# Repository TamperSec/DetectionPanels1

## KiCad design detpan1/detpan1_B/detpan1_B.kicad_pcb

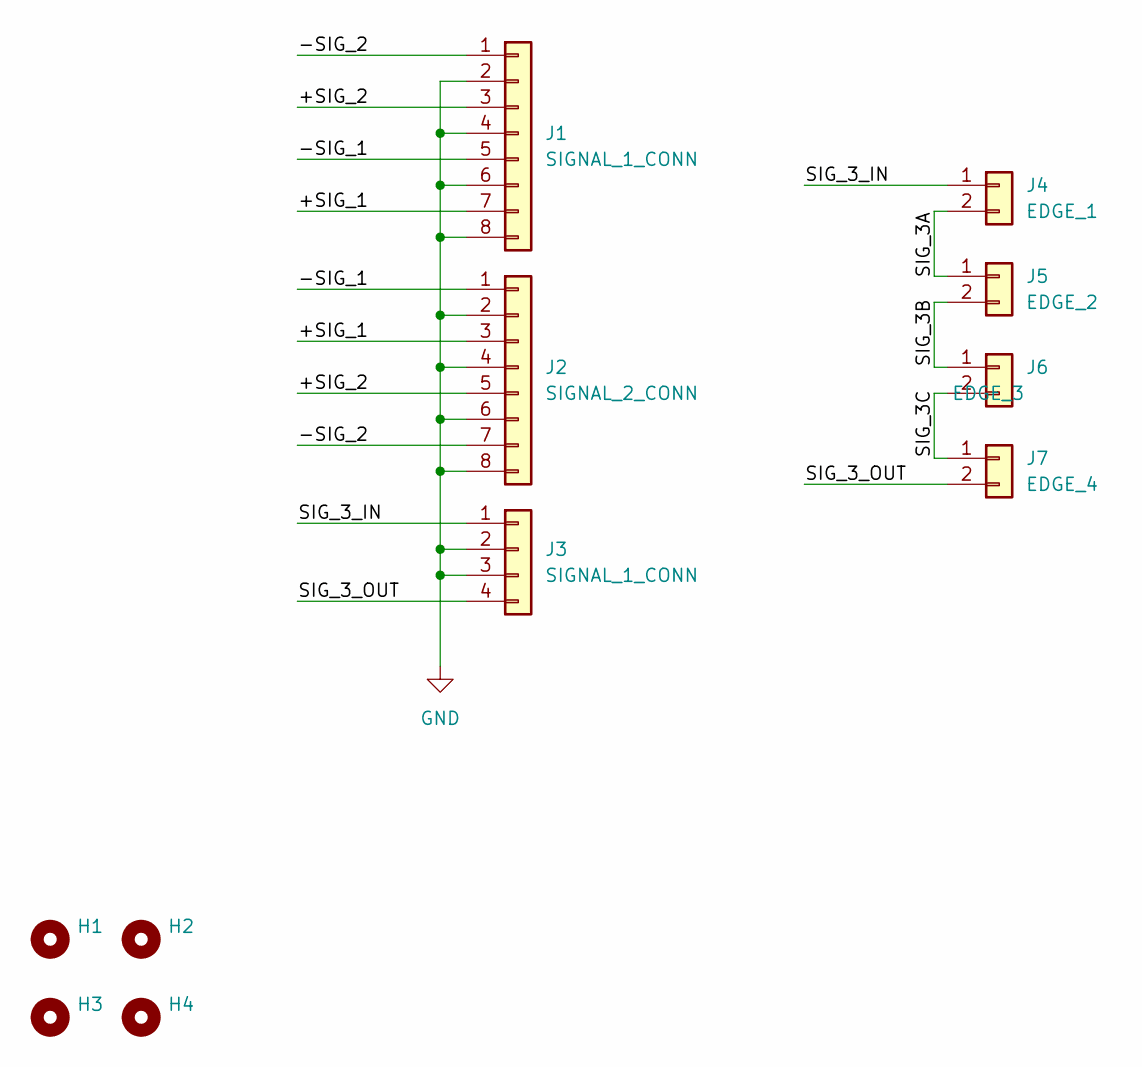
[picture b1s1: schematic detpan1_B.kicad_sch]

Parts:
H1, H2, H3, H4: MountingHole_3.2mm_M3
J1: SIGNAL_1_CONN; JST_GH_BM08B-GHS-TBT_1x08-1MP_P1.25mm_Vertical
J2: SIGNAL_2_CONN; JST_GH_BM08B-GHS-TBT_1x08-1MP_P1.25mm_Vertical
J3: SIGNAL_1_CONN; JST_GH_BM04B-GHS-TBT_1x04-1MP_P1.25mm_Vertical; JLCPCB Part # C225120
J4: EDGE_1; EDGE_CONN_IO
J5: EDGE_2; EDGE_CONN_IO
J6: EDGE_3; EDGE_CONN_IO
J7: EDGE_4; EDGE_CONN_IO

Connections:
/+SIG_1: J1.7, J2.3
/+SIG_2: J1.3, J2.5
/-SIG_1: J1.5, J2.1
/-SIG_2: J1.1, J2.7
/SIG_3A: J4.2, J5.1
/SIG_3B: J5.2, J6.1
/SIG_3C: J6.2, J7.1
/SIG_3_IN: J3.1, J4.1
/SIG_3_OUT: J3.4, J7.2
GND: J1.2, J1.4, J1.6, J1.8, J2.2, J2.4, J2.6, J2.8, J3.2, J3.3

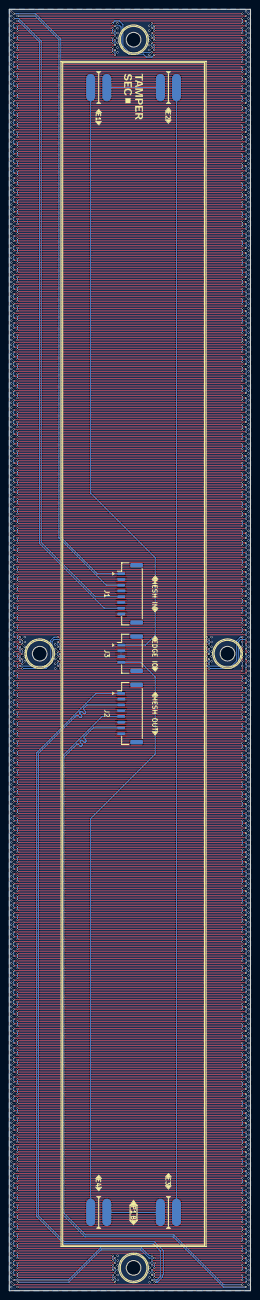
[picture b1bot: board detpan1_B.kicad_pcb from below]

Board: 4 copper layers, 52.4 x 278.4 mm, 11 parts (7 on the bottom side), 10 nets.

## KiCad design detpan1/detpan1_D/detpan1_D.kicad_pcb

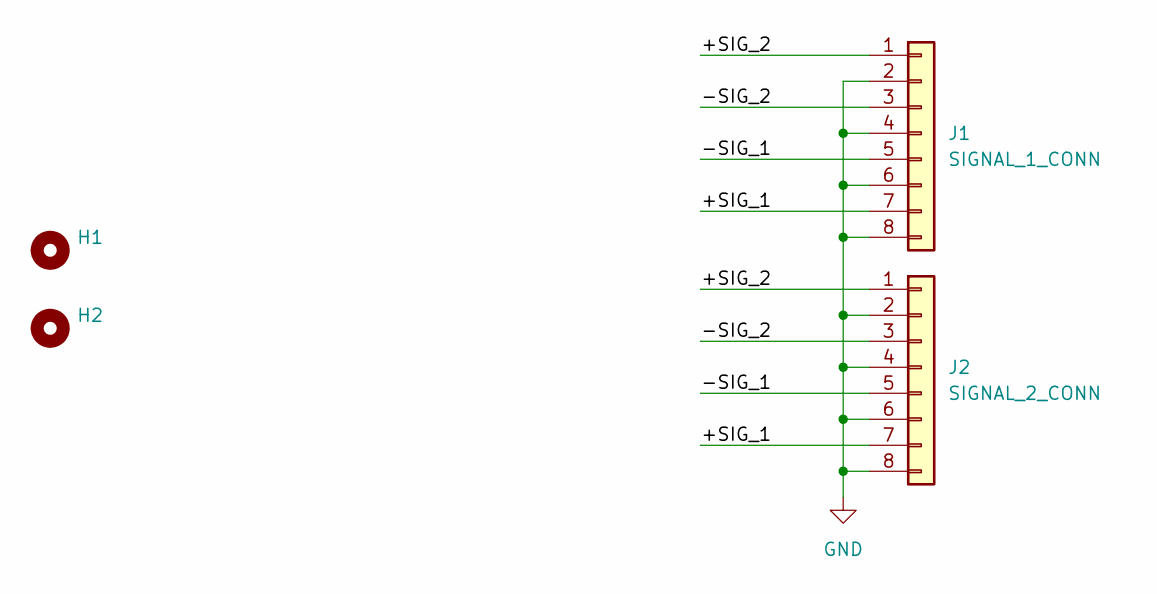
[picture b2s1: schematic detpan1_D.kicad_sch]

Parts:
H1, H2: MountingHole_3.2mm_M3
J1: SIGNAL_1_CONN; JST_GH_BM08B-GHS-TBT_1x08-1MP_P1.25mm_Vertical
J2: SIGNAL_2_CONN; JST_GH_BM08B-GHS-TBT_1x08-1MP_P1.25mm_Vertical

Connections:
/+SIG_1: J1.7, J2.7
/+SIG_2: J1.1, J2.1
/-SIG_1: J1.5, J2.5
/-SIG_2: J1.3, J2.3
GND: J1.2, J1.4, J1.6, J1.8, J2.2, J2.4, J2.6, J2.8

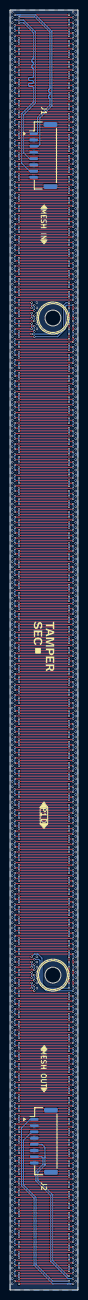
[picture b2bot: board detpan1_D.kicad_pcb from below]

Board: 4 copper layers, 13.6 x 256.8 mm, 4 parts (2 on the bottom side), 5 nets.

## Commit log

2025-07-28 Completed Detection Panels A-F
2025-08-14 Generate 3D STEP models for all panels.
